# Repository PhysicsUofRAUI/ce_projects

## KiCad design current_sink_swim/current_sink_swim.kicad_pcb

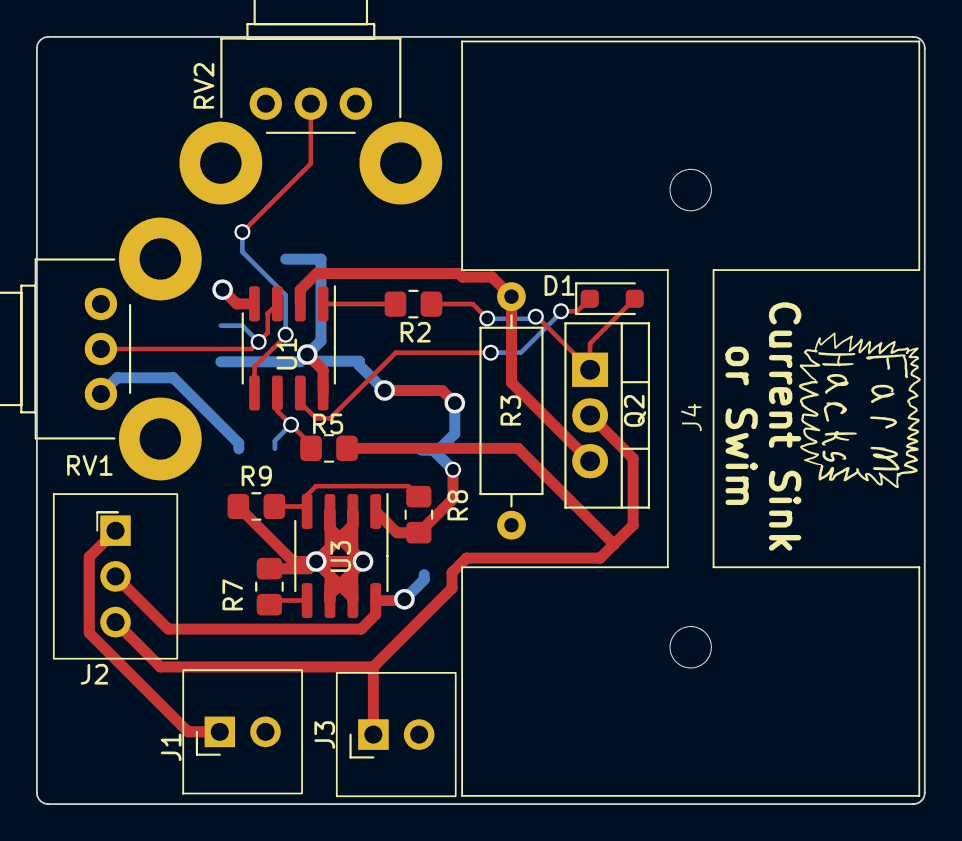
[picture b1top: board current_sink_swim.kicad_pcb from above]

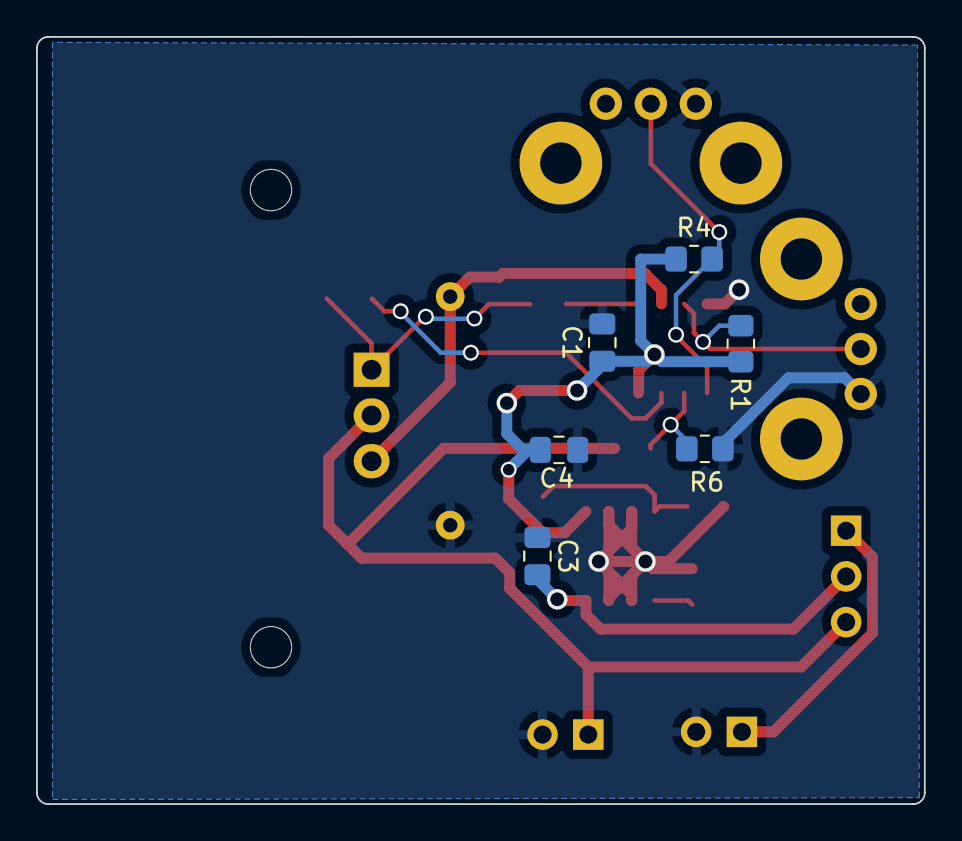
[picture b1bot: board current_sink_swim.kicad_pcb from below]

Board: 2 copper layers, 49.3 x 42.6 mm, 22 parts (6 on the bottom side), 14 nets.

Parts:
C1, C3, C4: C; C_0805_2012Metric_Pad1.18x1.45mm_HandSolder
D1: D; D_SOD-323_HandSoldering
J1, J3: Conn_01x02_Socket; te_2.54_2_pin_connector
J2: Conn_01x03_Socket; te_2.54mm_3_pin
J4: Conn_01x01_Pin; FAT-220
Q2: IRF540N; TO-220-3_Vertical
R1: 7.5k; R_0805_2012Metric_Pad1.20x1.40mm_HandSolder
R2, R6: 1k; R_0805_2012Metric_Pad1.20x1.40mm_HandSolder
R3: 0.1; R_Axial_DIN0309_L9.0mm_D3.2mm_P12.70mm_Horizontal
R4: 2.87k; R_0805_2012Metric_Pad1.20x1.40mm_HandSolder
R5: 9k; R_0805_2012Metric_Pad1.20x1.40mm_HandSolder
R7: 0; R_0805_2012Metric_Pad1.20x1.40mm_HandSolder
R8: 27k; R_0805_2012Metric_Pad1.20x1.40mm_HandSolder
R9: 21.5k; R_0805_2012Metric_Pad1.20x1.40mm_HandSolder
RV1, RV2: R_Potentiometer; Potentiometer_Bourns_PTV09A-2_Single_Horizontal
U1: LMV358; SOIC-8_3.9x4.9mm_P1.27mm
U3: TC1016; SOIC-8_3.9x4.9mm_P1.27mm

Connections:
2.7V: C1.1, C4.2, R1.1, R4.1, R8.2, U1.8 (V+), U3.1 (VO)
/ Current Control/FETGate: D1.2 (A), Q2.1 (G), R2.2
Current_Sink+: J2.3, J3.1, Q2.2 (D), R5.1
Current_Sink-: C1.2, C3.1, C4.1, J1.2, J3.2, R3.2, R6.2, R7.1, R9.1, RV1.3, RV2.3, U1.4 (V-), U3.2 (GND), U3.3 (GND), U3.6 (GND), U3.7 (GND)
unnamed: D1.1 (K), U1.7
unnamed: J1.1, J2.1
unnamed: Q2.3 (S), R3.1, U1.2 (-)
unnamed: R2.1, U1.1
unnamed: R1.2, RV1.2, U1.3 (+)
unnamed: R4.2, RV2.2, U1.5 (+)
unnamed: R5.2, R6.1, U1.6 (-)
unnamed: R8.1, R9.2, U3.4 (ADJ)
unnamed: R7.2, U3.5 (INHIBIT)
Vin: C3.2, J2.2, U3.8 (VI)

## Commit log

2023-07-08 Kicad schematic creation
2023-07-08 add base schematic
2023-07-08 add gitignore
2023-07-14 add hierarchical sheets
2023-07-28 re-annotate schematic
2023-07-28 assign footprints and start layout
2023-07-28 add heat sink
2023-07-28 created a rough board outline
2023-07-29 add correct pot symbols
2023-07-29 clean up potentiometer circuits
2023-07-29 update pcb layout with the new pot circuit
2023-07-29 improve layout
2023-07-30 first attempt at layout. Probably will be ripped up
2023-07-30 move some componenets around and route all traces
2023-07-30 relayed out one resistor
2023-07-31 initial generation of gerber files
2023-07-31 add part numbers and BOM
